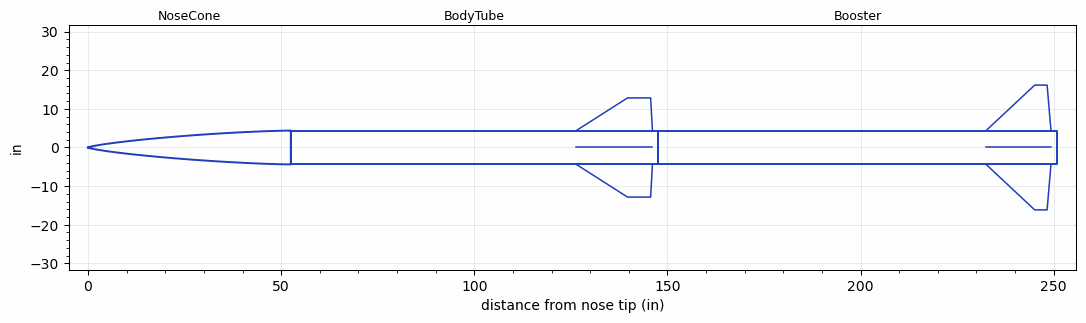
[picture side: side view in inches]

<RASAeroDocument>
 <FileVersion>2</FileVersion>
 <RocketDesign>
  <NoseCone>
   <Length>52.5</Length>
   <Diameter>8.75</Diameter>
   <Shape>Von Karman Ogive</Shape>
   <Location>0</Location>
  </NoseCone>
  <BodyTube>
   <Length>95.123806</Length>
   <Diameter>8.75</Diameter>
   <Location>52.5</Location>
   <Fin>
    <Count>4</Count>
    <Chord>19.710304</Chord>
    <Span>8.4652476</Span>
    <SweepDistance>13.260919</SweepDistance>
    <TipChord>5.991435</TipChord>
    <Thickness>0.5</Thickness>
    <LERadius>0.5</LERadius>
    <Location>21.210304</Location>
    <AirfoilSection>Double Wedge</AirfoilSection>
    <FX1>1</FX1>
    <FX3>1</FX3>
   </Fin>
  </BodyTube>
  <Booster>
   <Length>103.18729</Length>
   <Diameter>8.75</Diameter>
   <InsideDiameter>8.75</InsideDiameter>
   <Location>147.62381</Location>
   <ShoulderLength>0</ShoulderLength>
   <Fin>
    <Count>4</Count>
    <Chord>16.807879</Chord>
    <Span>11.77965</Span>
    <SweepDistance>12.592957</SweepDistance>
    <TipChord>3.210853</TipChord>
    <Thickness>0.5</Thickness>
    <LERadius>0.5</LERadius>
    <Location>18.307879</Location>
    <AirfoilSection>Double Wedge</AirfoilSection>
    <FX1>1</FX1>
    <FX3>1</FX3>
   </Fin>
  </Booster>
  <Surface>Smooth (Zero Roughness)</Surface>
  <ModifiedBarrowman>False</ModifiedBarrowman>
  <Turbulence>False</Turbulence>
  <UseBooster1>False</UseBooster1>
  <UseBooster2>False</UseBooster2>
 </RocketDesign>
 <LaunchSite>
  <Altitude>2050</Altitude>
  <Pressure>0</Pressure>
  <RodAngle>0</RodAngle>
  <RodLength>24</RodLength>
  <Temperature>90</Temperature>
  <WindSpeed>0</WindSpeed>
 </LaunchSite>
 <Recovery>
  <Altitude1>1000</Altitude1>
  <Altitude2>1000</Altitude2>
  <DeviceType1>Parachute</DeviceType1>
  <DeviceType2>None</DeviceType2>
  <Event1>True</Event1>
  <Event2>False</Event2>
  <Size1>48</Size1>
  <Size2>1</Size2>
  <EventType1>Apogee</EventType1>
  <EventType2>None</EventType2>
  <CD1>0.97</CD1>
  <CD2>1.33</CD2>
 </Recovery>
 <SimulationList>
  <Simulation>
   <SustainerEngine>Sustainer  (FS_PRO)</SustainerEngine>
   <SustainerLaunchWt>290.68166</SustainerLaunchWt>
   <SustainerNozzleDiameter>4.18</SustainerNozzleDiameter>
   <SustainerCG>113.01458</SustainerCG>
   <SustainerIgnitionDelay>16.077143</SustainerIgnitionDelay>
   <Booster1Engine>Booster  (FS_PRO)</Booster1Engine>
   <Booster1LaunchWt>567.41183</Booster1LaunchWt>
   <Booster1SeparationDelay>2</Booster1SeparationDelay>
   <Booster1IgnitionDelay>0</Booster1IgnitionDelay>
   <Booster1CG>165.22709</Booster1CG>
   <Booster1NozzleDiameter>4.18</Booster1NozzleDiameter>
   <IncludeBooster1>True</IncludeBooster1>
   <Booster2Delay>0</Booster2Delay>
   <IncludeBooster2>False</IncludeBooster2>
  </Simulation>
 </SimulationList>
</RASAeroDocument>
